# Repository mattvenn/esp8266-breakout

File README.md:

# v3

* added pullup resistors for GPIO0 & CH_PD

# v2

* silkscreen of 4&5 changed
* silkscreen of ftdi pinout added

# v1

* bug: pins 4&5 switched - silkscreen of the modules lines up, but not working in SW
See adafruit's huzzah: https://learn.adafruit.com/adafruit-huzzah-esp8266-breakout/using-nodemcu-lua
* smt switch, which one from farnell?
* power led & resistor

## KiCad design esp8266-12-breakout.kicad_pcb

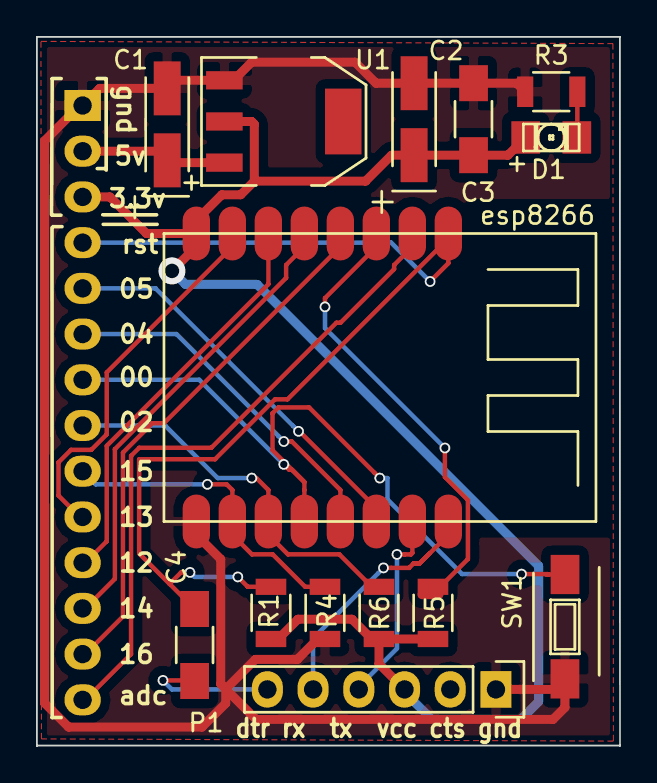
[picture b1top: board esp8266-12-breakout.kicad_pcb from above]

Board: 2 copper layers, 32.4 x 39.4 mm, 15 parts (1 on the bottom side), 19 nets.

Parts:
C1, C2: 10uf; TantalC_SizeA_EIA-3216_HandSoldering
C3: 0.1uf; C_1206_HandSoldering
C4: 1uf; C_1206_HandSoldering
D1: LED; LED-1206
P1: ftdi; Pin_Header_Straight_1x06
P2: CONN_01X14; Pin_Header_Straight_1x14
R1, R4, R5, R6: 10k; R_1206
R3: 68r; R_1206
SW1: SW_PUSH; SW_SPST_FSMSM
U1: AP1117D33; SOT-223
esp8266: U2; esp8266-12

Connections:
+3V3: C2.1, C3.1, D1.2, P1.3, P2.3, R1.1, R4.1, R5.1, U1.2, esp8266.8
+5V: C1.1, P2.2, U1.3
/adc: P2.14, esp8266.2
/ch_pd: R5.2, esp8266.3
/gpio0: P2.7, SW1.1, esp8266.12
/gpio2: P2.8, R4.2, esp8266.11
/gpio4: P2.6, esp8266.13
/gpio5: P2.5, esp8266.14
/gpio12: P2.11, esp8266.6
/gpio13: P2.10, esp8266.7
/gpio14: P2.12, esp8266.5
/gpio15: P2.9, R6.1, esp8266.10
/gpio16: P2.13, esp8266.4
/reset: C4.2, P2.4, R1.2, esp8266.1
/rx: P1.4, esp8266.15
/tx: P1.5, esp8266.16
GND: C1.2, C2.2, C3.2, P1.1, P2.1, R3.2, R6.2, SW1.2, U1.1, esp8266.9
unnamed: C4.1, P1.6
unnamed: D1.1, R3.1

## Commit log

2015-07-25 sent to fab
2015-07-25 fixed gpio 4/5 mixup
2015-07-25 trying to unify libs
2015-07-26 added reset pin to breakout for deepsleep
2015-08-11 removed rescue lib
2015-08-17 added bom
2015-08-20 4&5 pin flip bug
2015-09-01 added header part #
2015-09-01 serial silk screen and v2
2015-09-01 swapped gpio 4&5
2015-09-01 notes
2016-04-19 v3 added pull up resistors for gpio0 & 2
2016-04-19 readme & gerbers
2016-04-19 yaml
2016-04-19 1click bom
2016-04-19 removed old bom
2016-04-19 Run auto-complete on 1-click-BOM
2016-05-25 Update to new kitnic conventions
2016-05-26 Rename description to summary in kitnic.yaml
2016-08-13 Fix board outline and re-plot with newest KiCad
2016-08-13 Really strictly align outline
